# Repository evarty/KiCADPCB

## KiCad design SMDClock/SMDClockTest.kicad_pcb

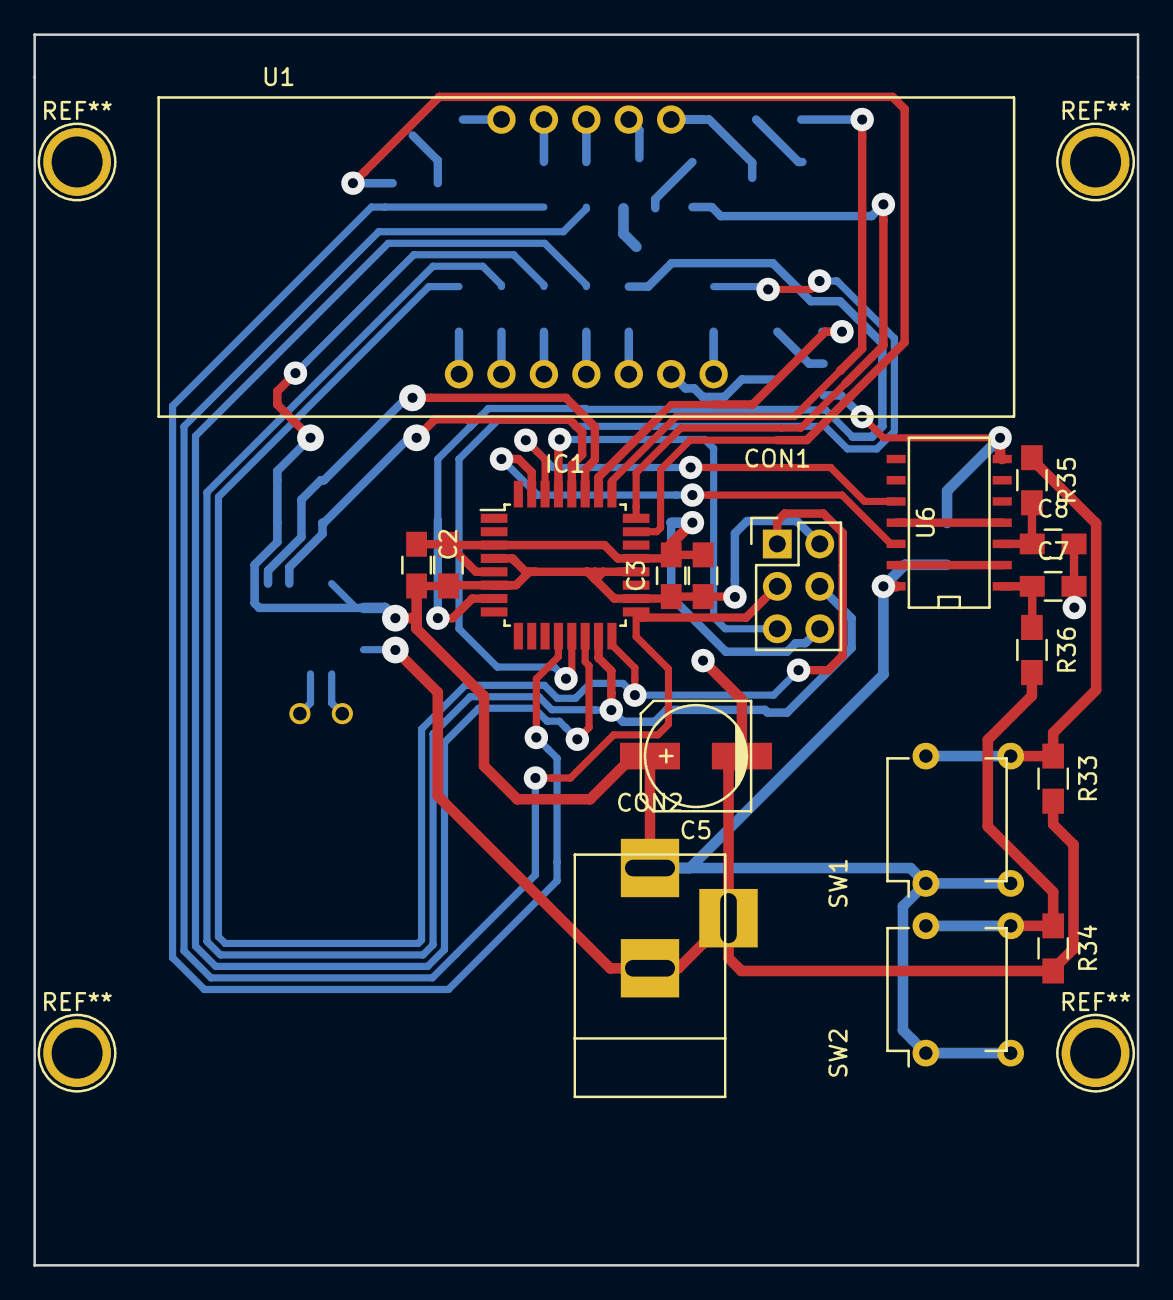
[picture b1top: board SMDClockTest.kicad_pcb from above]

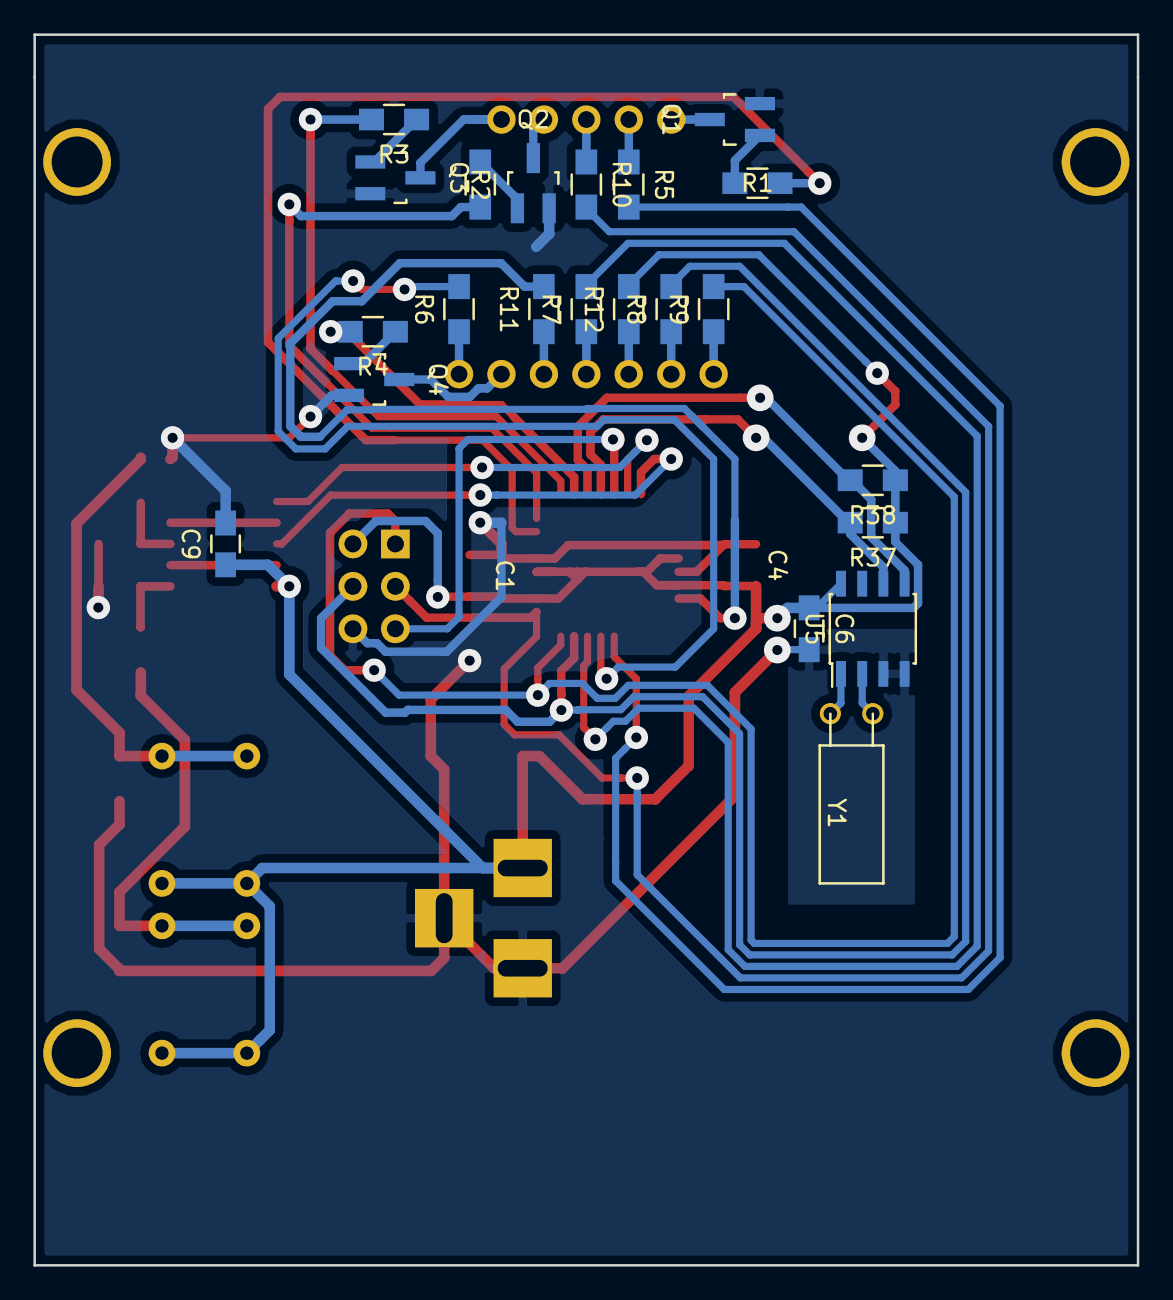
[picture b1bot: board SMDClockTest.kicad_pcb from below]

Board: 2 copper layers, 66.0 x 73.7 mm, 40 parts (22 on the bottom side), 42 nets.

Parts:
C1, C2, C6, C9: .1u; C_0805_HandSoldering
C3, C4: 10n; C_0805_HandSoldering
C5: 100u; c_elec_6.3x5.3
C7, C8: .47u; C_0805_HandSoldering
CON1: AVR-ISP-6; Pin_Header_Straight_2x03
CON2: BARREL_JACK
IC1: ATMEGA328P-A; TQFP-32_7x7mm_Pitch0.8mm
Q1, Q2, Q3, Q4: Q_NPN_BEC; SOT-23_Handsoldering
R1, R2, R3, R4: 1k; R_0805_HandSoldering
R5, R6, R7, R8, R9, R10, R11, R12: 470R; R_0805_HandSoldering
R33, R34: 10K; R_0805_HandSoldering
R35, R36, R37, R38: 4K7; R_0805_HandSoldering
SW1, SW2: PushButton
U1: HDSP-B03E_LED_Clock_Display; DHDSP-B03E_Footprint
U5: DS1307; SOIC-8_3.9x4.9mm_Pitch1.27mm
U6: 74LS14; SOIC-14_N
Y1: Crystal; Crystal_Watch

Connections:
+5V: C1.1, C2.1, C3.1, C4.1, C5.1, C6.1, C9.1, CON1.2, CON2.1, IC1.4, IC1.6, IC1.18, IC1.20, R12.2, R37.1, R38.1, SW1.1, SW1.2, SW2.1, SW2.2, U5.8, U6.14
/1: IC1.12, R5.2
/2: IC1.13, R6.2
/3: IC1.14, R7.2
/7: IC1.7, R11.2
Button1: IC1.30, U6.10
Button2: IC1.31, U6.12
GND: C1.2, C2.2, C3.2, C4.2, C5.2, C6.2, C7.2, C8.2, C9.2, CON1.6, CON2.2, CON2.3, IC1.3, IC1.5, IC1.21, Q1.2, Q2.2, Q3.2, Q4.2, R33.2, R34.2, U5.3, U5.4, U6.7
MISO: CON1.1, IC1.16, R9.2
MOSI: CON1.4, IC1.15, R8.2
unnamed: C7.1, R36.1, U6.1
unnamed: C8.1, R35.2, U6.3
unnamed: IC1.23, R1.2
unnamed: IC1.24, R2.2
unnamed: IC1.25, R3.2
unnamed: IC1.26, R4.2
unnamed: Q1.1, R1.1
unnamed: Q1.3, U1.12
unnamed: Q2.1, R2.1
unnamed: Q2.3, U1.9
unnamed: Q3.1, R3.1
unnamed: Q3.3, U1.8
unnamed: Q4.1, R4.1
unnamed: Q4.3, U1.6
unnamed: R5.1, U1.11
unnamed: R6.1, U1.7
unnamed: R7.1, U1.4
unnamed: R8.1, U1.2
unnamed: R9.1, U1.1
unnamed: R10.1, U1.10
unnamed: R11.1, U1.5
unnamed: R12.1, U1.3
unnamed: R33.1, R35.1, SW1.3, SW1.4
unnamed: R34.1, R36.2, SW2.3, SW2.4
unnamed: U5.1, Y1.1
unnamed: U5.2, Y1.2
unnamed: U6.4, U6.11
unnamed: U6.2, U6.13
RST: CON1.5, IC1.29
SCK: CON1.3, IC1.17, R10.2
SCL: IC1.28, R37.2, U5.6
SDA: IC1.27, R38.2, U5.5

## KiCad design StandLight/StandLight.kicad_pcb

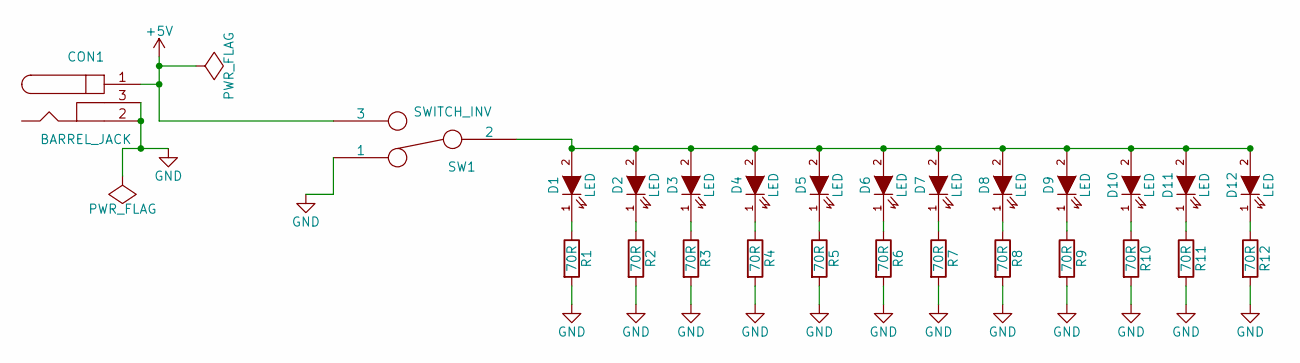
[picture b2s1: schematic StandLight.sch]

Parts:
CON1: BARREL_JACK
D1, D2, D3, D4, D5, D6, D7, D8, D9, D10, D11, D12: LED; LED-5MM
R1, R2, R3, R4, R5, R6, R7, R8, R9, R10, R11, R12: 70R; Resistor_Horizontal_RM20mm
SW1: SWITCH_INV; SW_Micro_SPST

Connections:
+5V: CON1.1, SW1.3
GND: CON1.2, CON1.3, R1.2, R2.2, R3.2, R4.2, R5.2, R6.2, R7.2, R8.2, R9.2, R10.2, R11.2, R12.2, SW1.1
unnamed: D1.1 (K), R1.1
unnamed: D1.2 (A), D2.2 (A), D3.2 (A), D4.2 (A), D5.2 (A), D6.2 (A), D7.2 (A), D8.2 (A), D9.2 (A), D10.2 (A), D11.2 (A), D12.2 (A), SW1.2
unnamed: D2.1 (K), R2.1
unnamed: D3.1 (K), R3.1
unnamed: D4.1 (K), R4.1
unnamed: D5.1 (K), R5.1
unnamed: D6.1 (K), R6.1
unnamed: D7.1 (K), R7.1
unnamed: D8.1 (K), R8.1
unnamed: D9.1 (K), R9.1
unnamed: D10.1 (K), R10.1
unnamed: D11.1 (K), R11.1
unnamed: D12.1 (K), R12.1

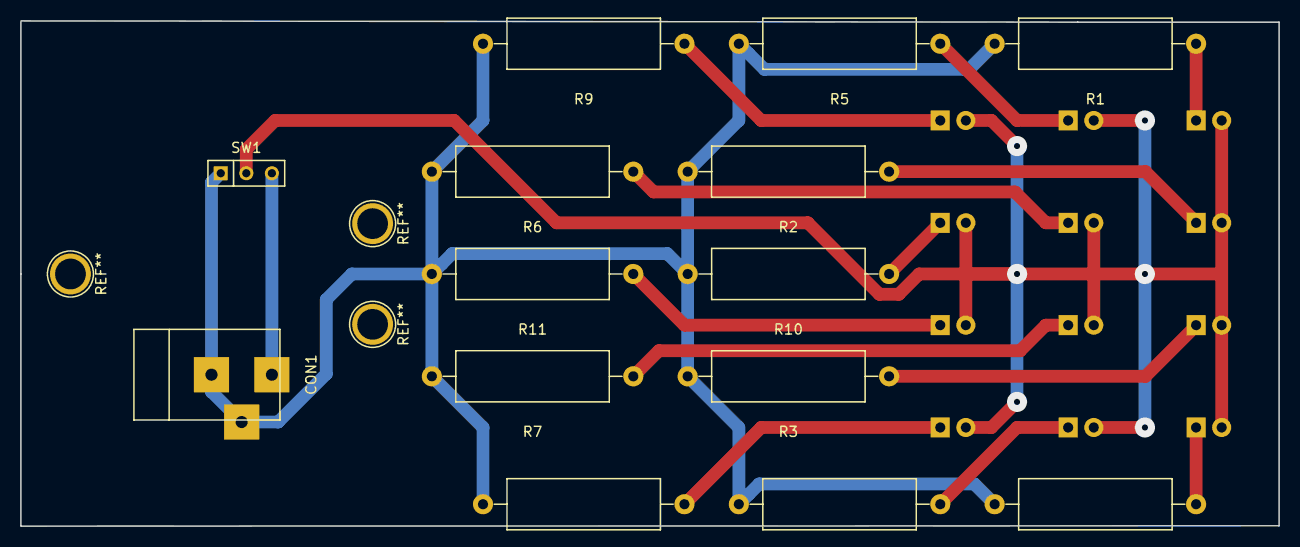
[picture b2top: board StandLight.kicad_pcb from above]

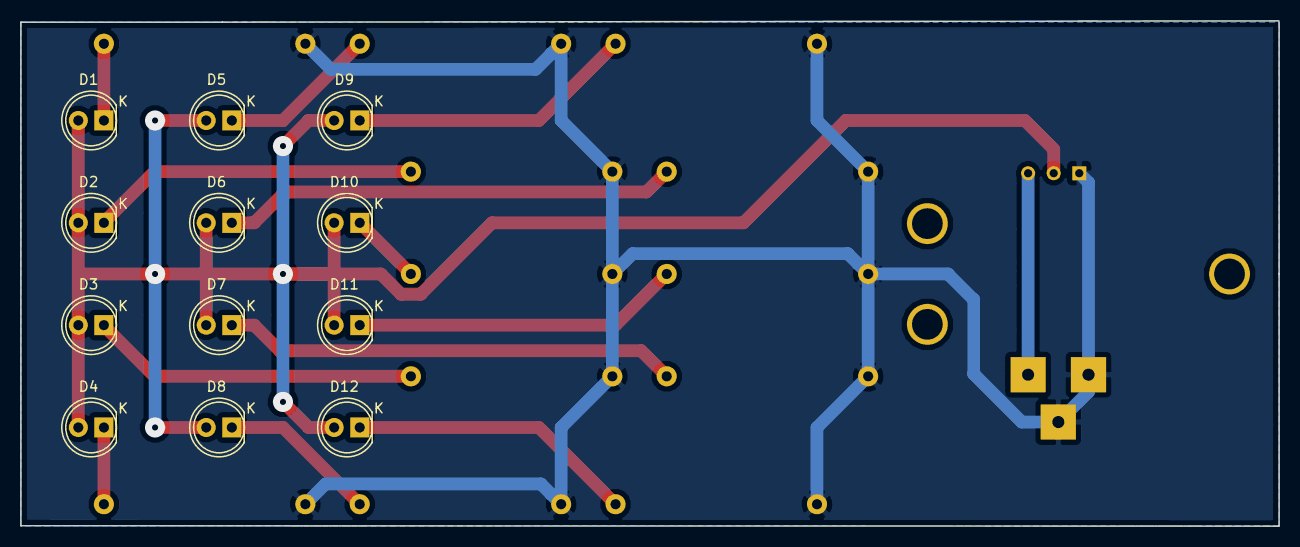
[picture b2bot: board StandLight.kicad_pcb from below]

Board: 2 copper layers, 124.9 x 50.2 mm, 26 parts (12 on the bottom side), 15 nets.
